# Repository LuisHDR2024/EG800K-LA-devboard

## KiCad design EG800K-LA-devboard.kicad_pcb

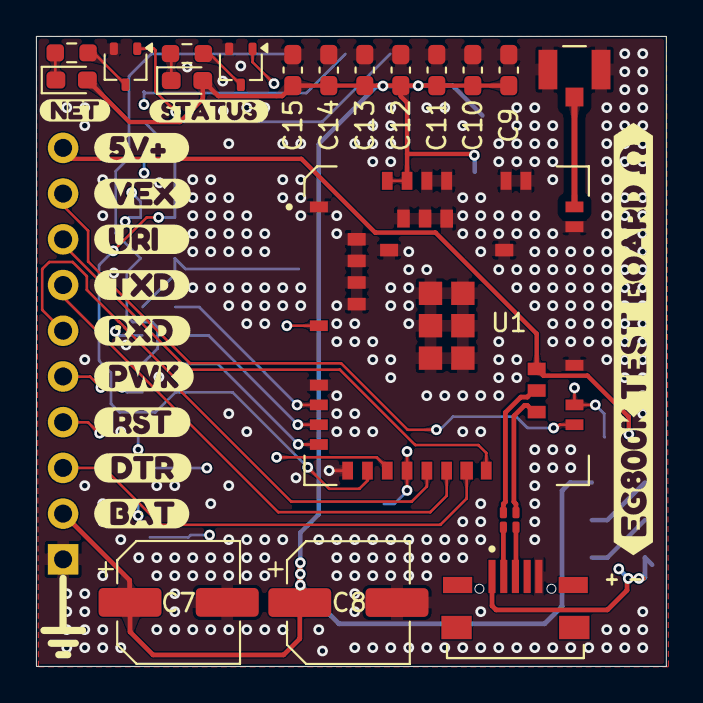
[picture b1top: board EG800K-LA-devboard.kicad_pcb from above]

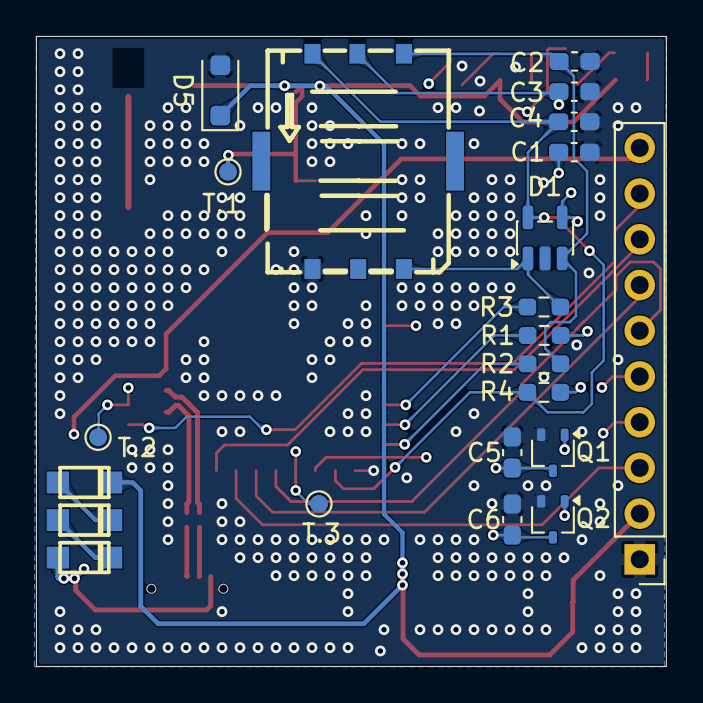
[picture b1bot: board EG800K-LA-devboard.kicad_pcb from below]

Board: 4 copper layers, 35.0 x 35.0 mm, 51 parts (19 on the bottom side), 32 nets.

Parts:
C1, C2, C3: 33pF; C_0603_1608Metric_Pad1.08x0.95mm_HandSolder
C4, C11: 100nf; C_0603_1608Metric_Pad1.08x0.95mm_HandSolder
C5, C6, C12: 10nf; C_0603_1608Metric_Pad1.08x0.95mm_HandSolder
C7, C8: 470uF; CP_Elec_6.3x7.7
C9: 47uf; C_0603_1608Metric_Pad1.08x0.95mm_HandSolder
C10: 33pf; C_0603_1608Metric_Pad1.08x0.95mm_HandSolder
C13: 0.1uf; C_0603_1608Metric_Pad1.08x0.95mm_HandSolder
C14: 1uf; C_0603_1608Metric_Pad1.08x0.95mm_HandSolder
C15: 10uf; C_0603_1608Metric_Pad1.08x0.95mm_HandSolder
D1: ESDA6V1SC5; SOT-23-5
D2, D3, D4: KUU SS36; KUU_SS36_foot
D5: SMFJ5.0A; D_SOD-123F
D6, D7: LED; LED_0603_1608Metric_Pad1.05x0.95mm_HandSolder
J1: U.FL-R-SMT_10_; U.FL-R-SMT_10_-foot
J2: MICROQTJ; MICROQTJ-foot
J4: Conn_01x11_Pin; PinHeader_1x10_P2.54mm_Vertical
NANO-SIM-0501A-P1: NANO-SIM-0501A-P; nano-sim-0501a-p_foot
Q1, Q2, Q4, Q5: DTC143ZUAT106; SOT-323_SC-70
R1, R2, R3: 0; R_0603_1608Metric_Pad0.98x0.95mm_HandSolder
R4: 15k; R_0603_1608Metric_Pad0.98x0.95mm_HandSolder
R5, R6: 22; R_0201_0603Metric_Pad0.64x0.40mm_HandSolder
R7, R8: 2.2k; R_0603_1608Metric_Pad0.98x0.95mm_HandSolder
U1: EG800KEULC-I03-SNNSA; Quectel_EG800K_foot_recorted
kibuzzard-6A1B8E1D: G***; kibuzzard-6A1B8E1D
kibuzzard-6A166AE0: G***; kibuzzard-6A166AE0
kibuzzard-6A166AEF: G***; kibuzzard-6A166AEF
kibuzzard-6A7814A6: G***; kibuzzard-6A7814A6
kibuzzard-6A7814D1: G***; kibuzzard-6A7814D1
kibuzzard-6A7814E0: G***; kibuzzard-6A7814E0
kibuzzard-6A7814F3: G***; kibuzzard-6A7814F3
kibuzzard-6A78147A: G***; kibuzzard-6A78147A
kibuzzard-6A78152D: G***; kibuzzard-6A78152D
kibuzzard-6A781493: G***; kibuzzard-6A781493
kibuzzard-6A781522: G***; kibuzzard-6A781522
kibuzzard-6A781536: G***; kibuzzard-6A781536

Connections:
+5V: D2.A, J2.1 (VCC), J4.10, U1.61 (USB_VBUS)
/DC 3.8v supply: C7.1, C8.1, C9.2, C10.2, C11.2, C12.2, C13.2, C14.2, C15.2, D4.C, D5.1 (K), D6.2 (A), D7.2 (A), J4.2, U1.42 (VBAT), U1.43 (VBAT__1)
/EG800K.NET_STATUS: Q5.1 (B), U1.16 (NET_STATUS)
/EG800K.PWRKEY: C5.2, Q1.3 (C), U1.7 (PWRKEY)
/EG800K.RESET: C6.2, Q2.3 (C), U1.15 (~RESET)
/EG800K.STATUS: Q4.1 (B), U1.25 (STATUS)
/EG800K.UART1_RXD: J4.6, U1.17 (MAIN_RXD)
/EG800K.UART1_Ri: J4.8, U1.20 (MAIN_RI)
/EG800K.UART1_TXD: J4.7, U1.18 (MAIN_TXD)
/EG800K.USB_D+: R6.2, U1.59 (USB_DP)
/EG800K.USB_D-: R5.2, U1.60 (USB_DM)
/EG800K.VDD_ETX: J4.9, U1.24 (VDD_EXT)
/HOST.EG800K.PWRKEY: J4.5, Q1.1 (B)
/HOST.EG800K.RESET: J4.4, Q2.1 (B)
/RF_ANT: J1.SIG, U1.35 (ANT_MAIN)
/SIM_CLK: R2.1, U1.13 (USIM_CLK)
/SIM_DATA: R3.1, U1.11 (USIM_DATA)
/SIM_RST: R1.1, U1.12 (USIM_RST)
/SIM_VDD: C4.2, D1.5 (K), NANO-SIM-0501A-P1.C1 (VCC), R4.2, U1.14 (USIM_VDD)
GND: C1.1, C2.1, C3.1, C4.1, C5.1, C6.1, C7.2, C8.2, C9.1, C10.1, C11.1, C12.1, C13.1, C14.1, C15.1, D1.2 (A), D5.2 (A), J1.G1, J1.G2, J2.5 (GND), J4.1, NANO-SIM-0501A-P1.C5 (GND), Q1.2 (E), Q2.2 (E), Q4.2 (E), Q5.2 (E), U1.1 (GND_1), U1.10 (GND_1__1), U1.27 (GND_1__2), U1.34 (GND_1__3), U1.36 (GND_1__4), U1.37 (GND_1__5), U1.40 (GND_1__6), U1.41 (GND_1__7), U1.45 (GND_1__8), U1.46 (GND_1__9), U1.47 (GND_1__10), U1.48 (GND_1__11), U1.70 (GND_2), U1.71 (GND_2__1), U1.72 (GND_2__2), U1.73 (GND_2__3), U1.88 (GND_2__4), U1.89 (GND_2__5), U1.90 (GND_2__6), U1.91 (GND_2__7), U1.92 (GND_2__8), U1.93 (GND_2__9), U1.94 (GND_2__10), U1.95 (GND_2__11)
unnamed: C1.2, R4.1
unnamed: D2.C, D3.A
unnamed: D3.C, D4.A
unnamed: D6.1 (K), R7.2
unnamed: D7.1 (K), R8.2
unnamed: J2.3 (D+), R6.1
unnamed: J2.2 (D-), R5.1
unnamed: C2.2, D1.3 (K), NANO-SIM-0501A-P1.C3 (CLK), R2.2
unnamed: D1.1 (K), NANO-SIM-0501A-P1.C7 (I/O), R3.2
unnamed: C3.2, D1.4 (K), NANO-SIM-0501A-P1.C2 (RST), R1.2
unnamed: Q4.3 (C), R7.1
unnamed: Q5.3 (C), R8.1

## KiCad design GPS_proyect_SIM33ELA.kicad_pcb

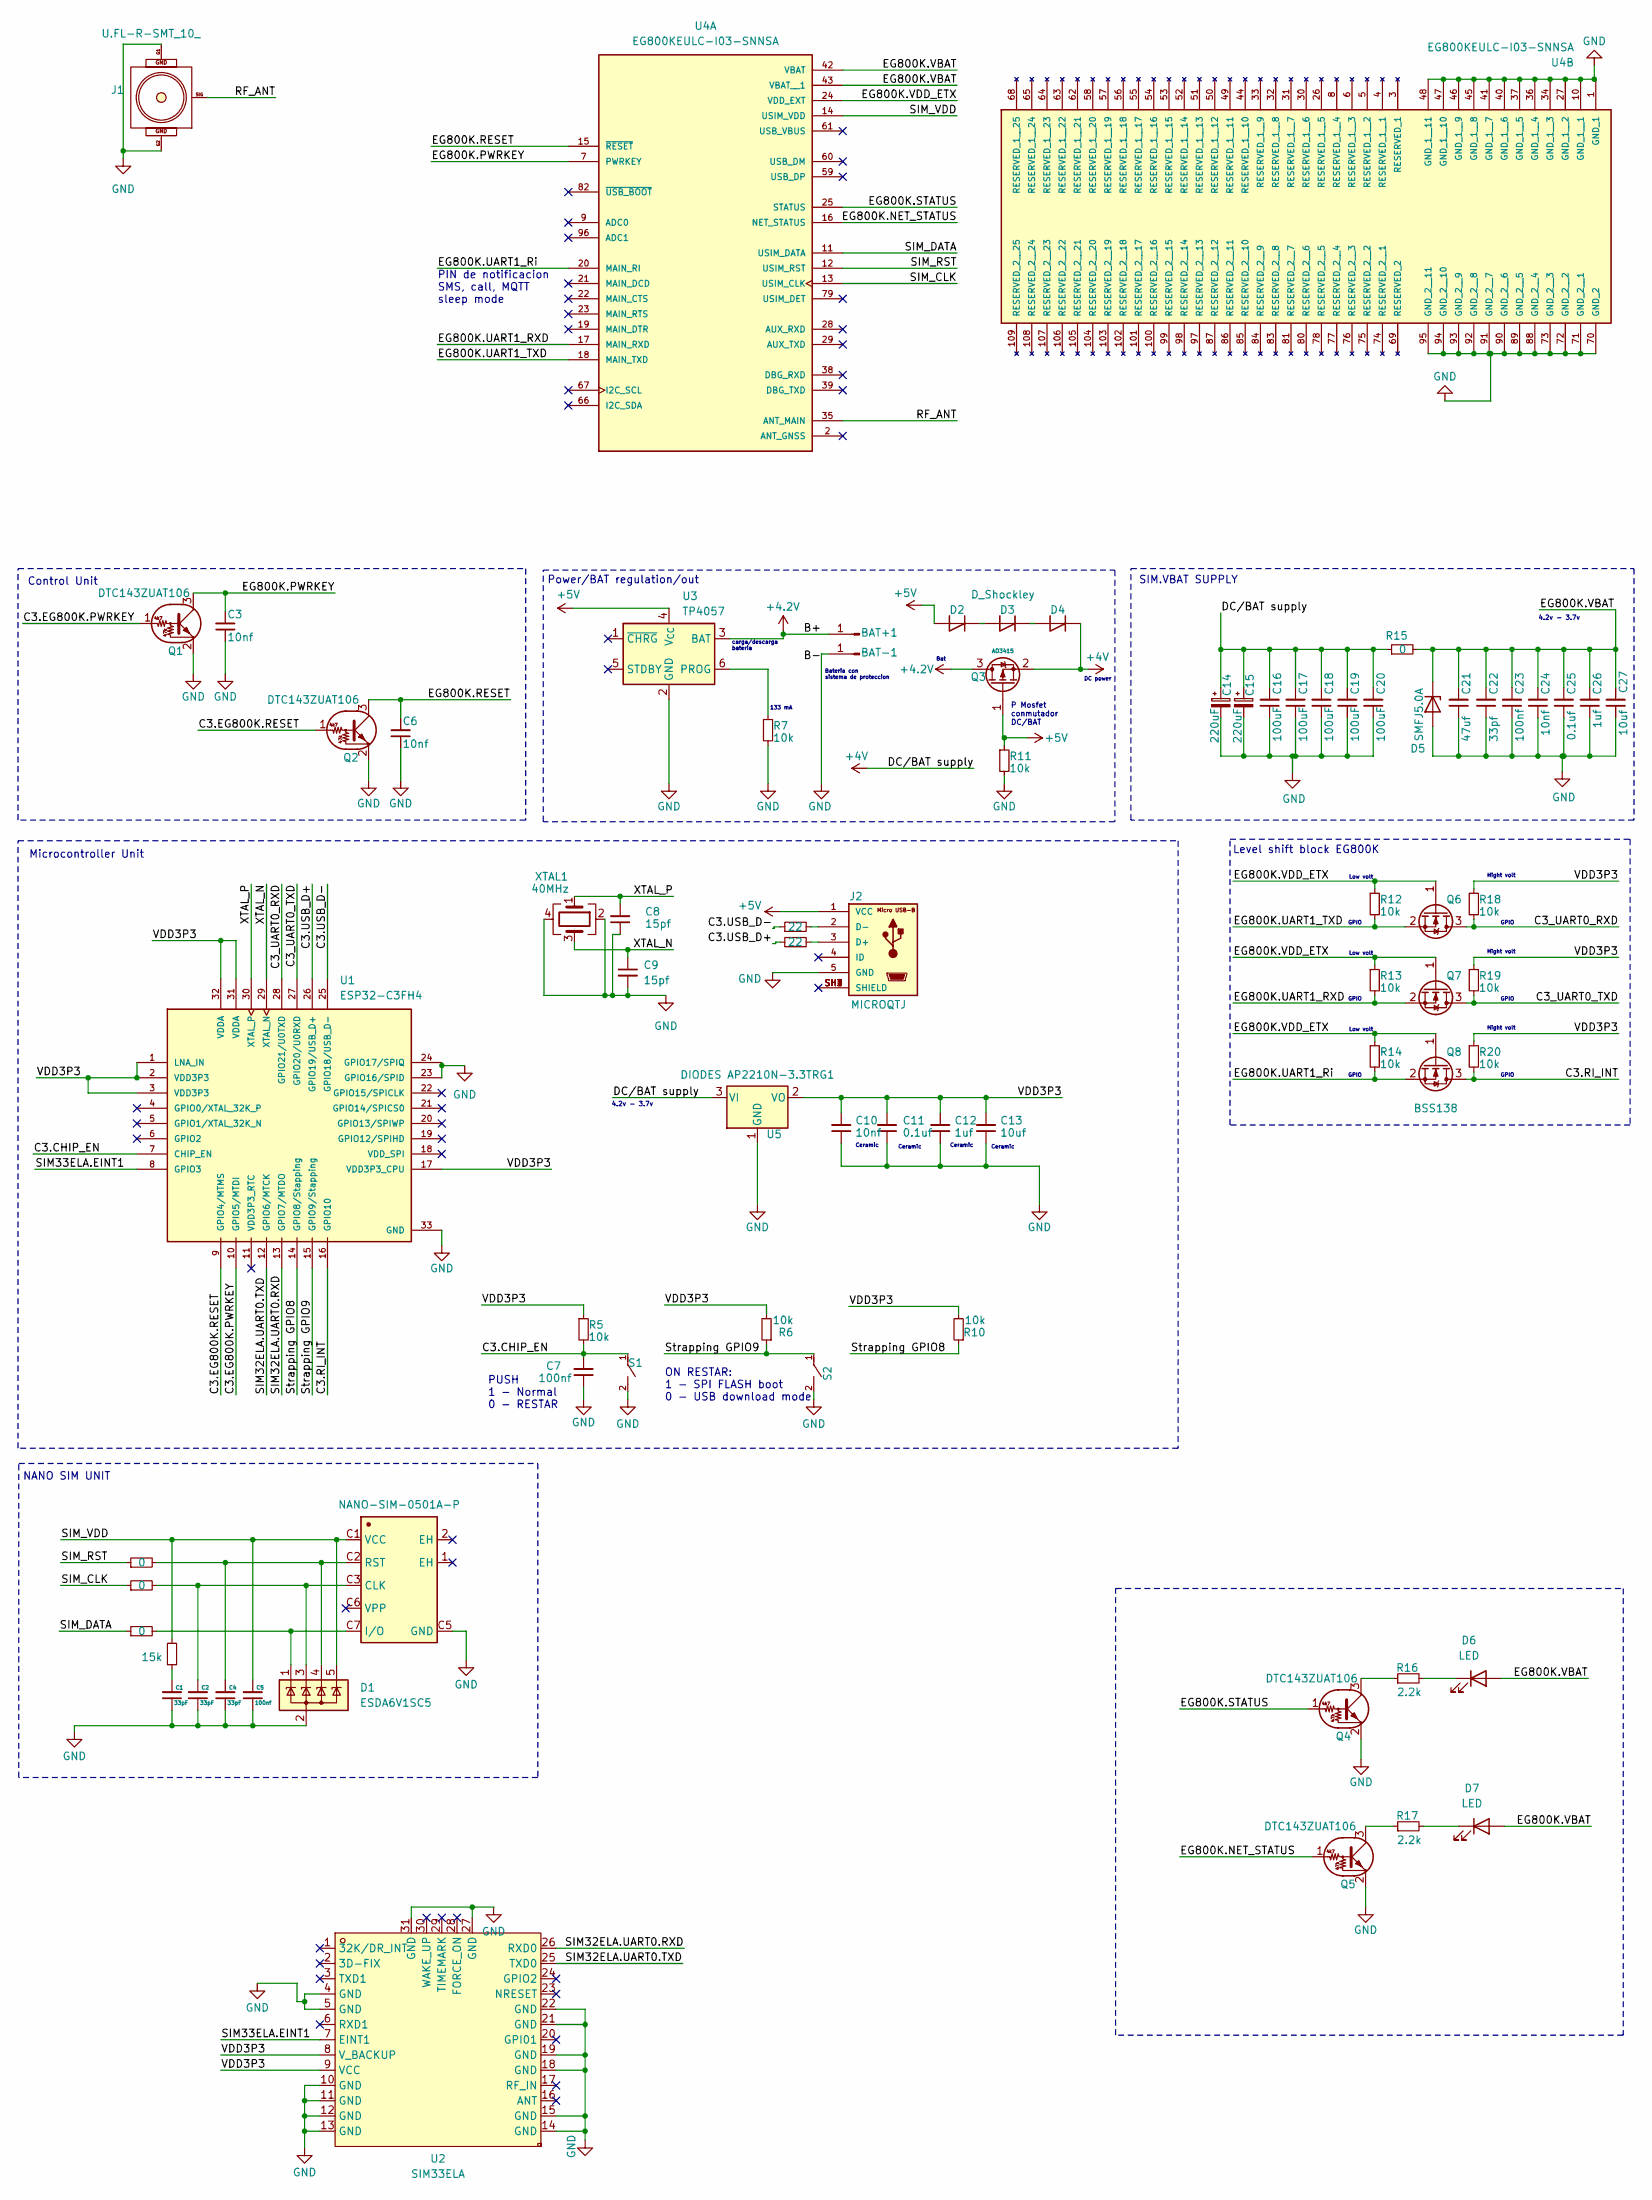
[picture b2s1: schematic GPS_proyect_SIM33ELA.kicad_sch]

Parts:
BAT+1: BAT+; SolderWirePad_1x01_SMD_2x4mm
BAT-1: BAT-; SolderWirePad_1x01_SMD_2x4mm
C1, C2, C4: 33pF; C_0603_1608Metric_Pad1.08x0.95mm_HandSolder; part number GRM1885C1H330JA01D
C3, C6, C10, C24: 10nf; C_0603_1608Metric_Pad1.08x0.95mm_HandSolder; part number GRM188R71H103KA01D
C5, C7, C23: 100nf; C_0603_1608Metric_Pad1.08x0.95mm_HandSolder; part number GRM188R71C104KA01D
C8, C9: 15pf; C_0603_1608Metric_Pad1.08x0.95mm_HandSolder; part number GRM1885C1H150JA01D
C11, C25: 0.1uf; C_0603_1608Metric_Pad1.08x0.95mm_HandSolder; part number GRM188R71C104KA01D
C12, C26: 1uf; C_0603_1608Metric_Pad1.08x0.95mm_HandSolder; part number GCM188R71E105KA64D
C13, C27: 10uf; C_0603_1608Metric_Pad1.08x0.95mm_HandSolder; part number GRM188R60J106KE47D
C14, C15: 220uF; CP_Elec_6.3x4.5; part number RVT0J221M0604
C16, C17, C18, C19, C20: 100uF; C_1210_3225Metric; part number GRM31CR60J107ME39L
C21: 47uf; C_0603_1608Metric_Pad1.08x0.95mm_HandSolder; part number GRM188R60J476ME15D
C22: 33pf; C_0603_1608Metric_Pad1.08x0.95mm_HandSolder; part number GRM1885C1H330JA01D
D1: ESDA6V1SC5; SOT-23-5; part number ESDA6V1SC5
D2, D3, D4: D_Shockley; D_SOD-123F; part number SS36
D5: SMFJ5.0A; D_SOD-123F; part number SMFJ5.0A
D6, D7: LED; LED_0603_1608Metric_Pad1.05x0.95mm_HandSolder; part number YLED0603R
J1: U.FL-R-SMT_10_; U.FL-R-SMT_10_-foot; part number U.FL-R-SMT-1(80)
J2: MICROQTJ; MICROQTJ-foot; part number MicroQTJ
NANO-SIM-0501A-P1: NANO-SIM-0501A-P; nano-sim-0501a-p_foot; part number NANO-SIM-0501A-P
Q1, Q2, Q4, Q5: DTC143ZUAT106; SOT-323_SC-70; part number DTC143ZUAT106
Q3: AO3415; SOT-23; part number AO3415
Q6, Q7, Q8: BSS138; SOT-23; part number BSS138-7-F
R1, R2, R3, R15: 0; R_0603_1608Metric_Pad0.98x0.95mm_HandSolder; part number CRCW06030000Z0EA
R4: 15k; R_0603_1608Metric_Pad0.98x0.95mm_HandSolder; part number CRCW06030000Z0EA
R5, R6, R7, R10, R11, R12, R13, R14, R18, R19, R20: 10k; R_0603_1608Metric_Pad0.98x0.95mm_HandSolder; part number CRCW060310K0FKEA
R8, R9: 22; R_0603_1608Metric_Pad0.98x0.95mm_HandSolder; part number CRCW060322R0FKEA
R16, R17: 2.2k; R_0603_1608Metric_Pad0.98x0.95mm_HandSolder; part number CRCW06032K20FKEAC
S1, S2: TS-1088-AR02016; SW_TS-1088-AR02016; part number TS-1088-AR02016
U1: ESP32-C3FH4; ESP32-C3FH4_foot; part number ESP32-C3FH4
U2: SIM33ELA; SIM33ELA_v2; part number SIM33ELA; LCSC Part C6488289
U3: TP4057; TSOT-23-6; part number TP4057
U4: EG800KEULC-I03-SNNSA; Quectel_EG800K_foot; part number Quectel EG800K-LA
U5: DIODES AP2210N-3.3TRG1; SOT-23; part number AP2210N-3.3TRG1
XTAL1: 40MHz; Crystal_SMD_3225-4Pin_3.2x2.5mm; part number XL2EL89CPI-111YLC-40M

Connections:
+4.2V: BAT+1.1, Q3.3 (D), U3.3 (BAT)
+4V: C14.1, C15.1, C16.2, C17.2, C18.2, C19.2, C20.2, D4.1 (K), Q3.2 (S), R15.1, U5.3 (VI)
+5V: D2.2 (A), J2.1 (VCC), Q3.1 (G), R11.1, U3.4 (V_{CC})
/C3.CHIP_EN: C7.2, R5.2, S1.1, U1.7 (CHIP_EN)
/C3.EG800K.PWRKEY: Q1.1 (B), U1.10 (GPIO5/MTDI)
/C3.EG800K.RESET: Q2.1 (B), U1.9 (GPIO4/MTMS)
/C3.RI_INT: Q8.3 (D), R20.2, U1.16 (GPIO10)
/C3.USB_D+: R9.1, U1.26 (GPIO19/USB_D+)
/C3.USB_D-: R8.1, U1.25 (GPIO18/USB_D-)
/C3_UART0_RXD: Q6.3 (D), R18.2, U1.28 (GPIO21/U0TXD)
/C3_UART0_TXD: Q7.3 (D), R19.2, U1.27 (GPIO20/U0RXD)
/EG800K.NET_STATUS: Q5.1 (B), U4.16 (NET_STATUS)
/EG800K.PWRKEY: C3.2, Q1.3 (C), U4.7 (PWRKEY)
/EG800K.RESET: C6.2, Q2.3 (C), U4.15 (~RESET)
/EG800K.STATUS: Q4.1 (B), U4.25 (STATUS)
/EG800K.UART1_RXD: Q7.2 (S), R13.2, U4.17 (MAIN_RXD)
/EG800K.UART1_Ri: Q8.2 (S), R14.2, U4.20 (MAIN_RI)
/EG800K.UART1_TXD: Q6.2 (S), R12.2, U4.18 (MAIN_TXD)
/EG800K.VBAT: C21.2, C22.2, C23.2, C24.2, C25.2, C26.2, C27.2, D5.1 (K), D6.2 (A), D7.2 (A), R15.2, U4.42 (VBAT), U4.43 (VBAT__1)
/EG800K.VDD_ETX: Q6.1 (G), Q7.1 (G), Q8.1 (G), R12.1, R13.1, R14.1, U4.24 (VDD_EXT)
/RF_ANT: J1.SIG, U4.35 (ANT_MAIN)
/SIM32ELA.UART0.RXD: U1.13 (GPIO7/MTDO), U2.26 (RXD0)
/SIM32ELA.UART0.TXD: U1.12 (GPIO6/MTCK), U2.25 (TXD0)
/SIM33ELA.EINT1: U1.8 (GPIO3), U2.7 (EINT1)
/SIM_CLK: R2.1, U4.13 (USIM_CLK)
/SIM_DATA: R3.1, U4.11 (USIM_DATA)
/SIM_RST: R1.1, U4.12 (USIM_RST)
/SIM_VDD: C5.2, D1.5 (K), NANO-SIM-0501A-P1.C1 (VCC), R4.2, U4.14 (USIM_VDD)
/Strapping GPIO8: R10.1, U1.14 (GPIO8/Stapping)
/Strapping GPIO9: R6.1, S2.1, U1.15 (GPIO9/Stapping)
/VDD3P3: C10.2, C11.2, C12.2, C13.2, R5.1, R6.2, R10.2, R18.1, R19.1, R20.1, U1.1 (LNA_IN), U1.2 (VDD3P3), U1.3 (VDD3P3), U1.17 (VDD3P3_CPU), U1.31 (VDDA), U1.32 (VDDA), U2.8 (V_BACKUP), U2.9 (VCC), U5.2 (VO)
/XTAL_N: C9.1, U1.29 (XTAL_N), XTAL1.3
/XTAL_P: C8.2, U1.30 (XTAL_P), XTAL1.1
GND: BAT-1.1, C1.1, C2.1, C3.1, C4.1, C5.1, C6.1, C7.1, C8.1, C9.2, C10.1, C11.1, C12.1, C13.1, C14.2, C15.2, C16.1, C17.1, C18.1, C19.1, C20.1, C21.1, C22.1, C23.1, C24.1, C25.1, C26.1, C27.1, D1.2 (A), D5.2 (A), J1.G1, J1.G2, J2.5 (GND), NANO-SIM-0501A-P1.C5 (GND), Q1.2 (E), Q2.2 (E), Q4.2 (E), Q5.2 (E), R7.2, R11.2, S1.2, S2.2, U1.23 (GPIO16/SPID), U1.24 (GPIO17/SPIQ), U1.33 (GND), U2.4 (GND), U2.5 (GND), U2.10 (GND), U2.11 (GND), U2.12 (GND), U2.13 (GND), U2.14 (GND), U2.15 (GND), U2.18 (GND), U2.19 (GND), U2.21 (GND), U2.22 (GND), U2.27 (GND), U2.31 (GND), U3.2 (GND), U4.1 (GND_1), U4.10 (GND_1__1), U4.27 (GND_1__2), U4.34 (GND_1__3), U4.36 (GND_1__4), U4.37 (GND_1__5), U4.40 (GND_1__6), U4.41 (GND_1__7), U4.45 (GND_1__8), U4.46 (GND_1__9), U4.47 (GND_1__10), U4.48 (GND_1__11), U4.70 (GND_2), U4.71 (GND_2__1), U4.72 (GND_2__2), U4.73 (GND_2__3), U4.88 (GND_2__4), U4.89 (GND_2__5), U4.90 (GND_2__6), U4.91 (GND_2__7), U4.92 (GND_2__8), U4.93 (GND_2__9), U4.94 (GND_2__10), U4.95 (GND_2__11), U5.1 (GND), XTAL1.2, XTAL1.4
unnamed: C1.2, R4.1
unnamed: D2.1 (K), D3.2 (A)
unnamed: D3.1 (K), D4.2 (A)
unnamed: D6.1 (K), R16.2
unnamed: D7.1 (K), R17.2
unnamed: J2.3 (D+), R9.2
unnamed: J2.2 (D-), R8.2
unnamed: C2.2, D1.3 (K), NANO-SIM-0501A-P1.C3 (CLK), R2.2
unnamed: D1.1 (K), NANO-SIM-0501A-P1.C7 (I/O), R3.2
unnamed: C4.2, D1.4 (K), NANO-SIM-0501A-P1.C2 (RST), R1.2
unnamed: Q4.3 (C), R16.1
unnamed: Q5.3 (C), R17.1
unnamed: R7.1, U3.6 (PROG)

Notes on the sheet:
SIM.VBAT SUPPLY
Ceramic
Bateria con sistema de proteccion
ON RESTAR: 1 - SPI FLASH boot 0 - USB download mode
carga/descarga bateria
Hight volt
GPIO
PUSH 1 - Normal 0 - RESTAR
Low volt
4.2v - 3.7v
Bat
P Mosfet conmutador DC/BAT
Control Unit
DC power
PIN de notificacion SMS, call, MQTT sleep mode
133 mA
Microcontroller Unit
Level shift block EG800K
Power/BAT regulation/out
NANO SIM UNIT

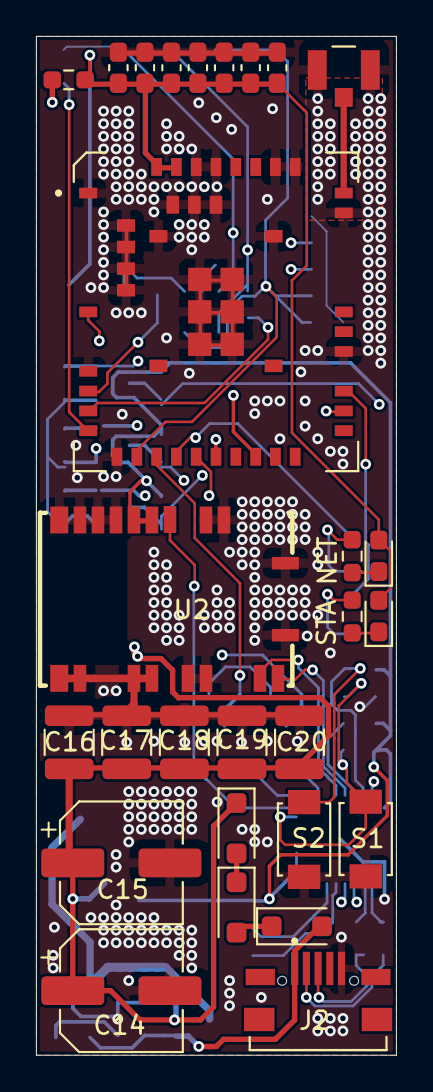
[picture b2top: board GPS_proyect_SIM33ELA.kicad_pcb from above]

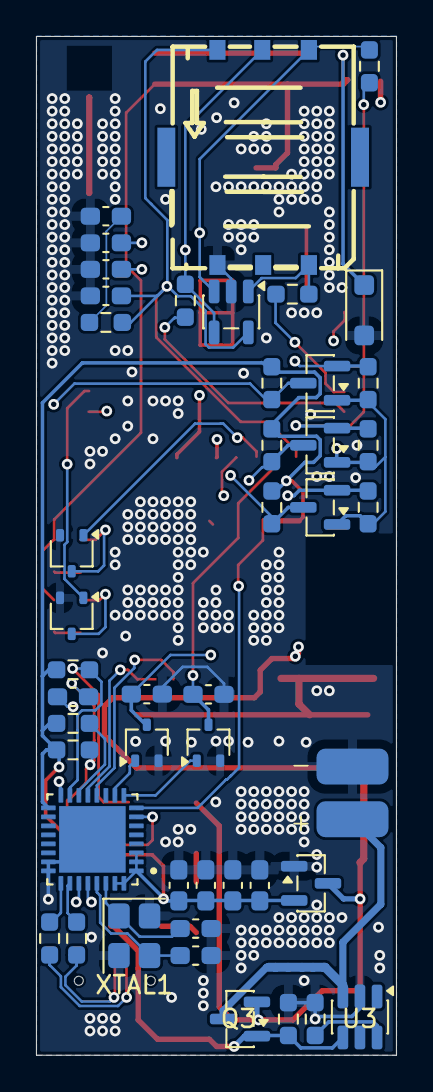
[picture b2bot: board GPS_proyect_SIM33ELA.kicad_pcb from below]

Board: 4 copper layers, 20.0 x 56.6 mm, 75 parts (47 on the bottom side), 46 nets.

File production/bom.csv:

Designator,Footprint,Quantity,Value,LCSC Part #
"C1, C2, C22, C4",0603,4,33pF,
C21,0603,1,47uf,
"C23, C5",0603,2,100nf,
"C24, C3, C6",0603,3,10nf,
C25,0603,1,0.1uf,
C26,0603,1,1uf,
C27,0603,1,10uf,
"C7, C8",CP_Elec_6.3x7.7,2,470uF,
D1,SOT-23-5,1,ESDA6V1SC5,
"D3, D4, D8",KUU_SS36_foot,3,KUU SS36,
D5,D_SOD-123F,1,SMFJ5.0A,
"D6, D7",0603,2,LED,
FL2,FILTER-SMD_4P-L2.0-W1.2-BL_DLW21H,1,Choke_CommonMode_FerriteCore_1243,
J1,U.FL-R-SMT_10_-foot,1,U.FL-R-SMT_10_,
J2,MICROQTJ-foot,1,MICROQTJ,
J5,PinHeader_1x08_P2.54mm_Vertical,1,Conn_01x08_Pin,
NANO-SIM-0501A-P1,nano-sim-0501a-p_foot,1,NANO-SIM-0501A-P,
"Q1, Q2, Q4, Q5",SOT-323_SC-70,4,DTC143ZUAT106,
"Q6, Q7, Q8",SOT-23,3,BSS138,
"R1, R15, R2, R3",0603,4,0,
"R12, R13, R14, R18, R19, R20",0603,6,10k,
"R16, R17",0603,2,2.2k,
R4,0603,1,15k,
U4,Quectel_EG800K_foot_recorted,1,EG800KEULC-I03-SNNSA,

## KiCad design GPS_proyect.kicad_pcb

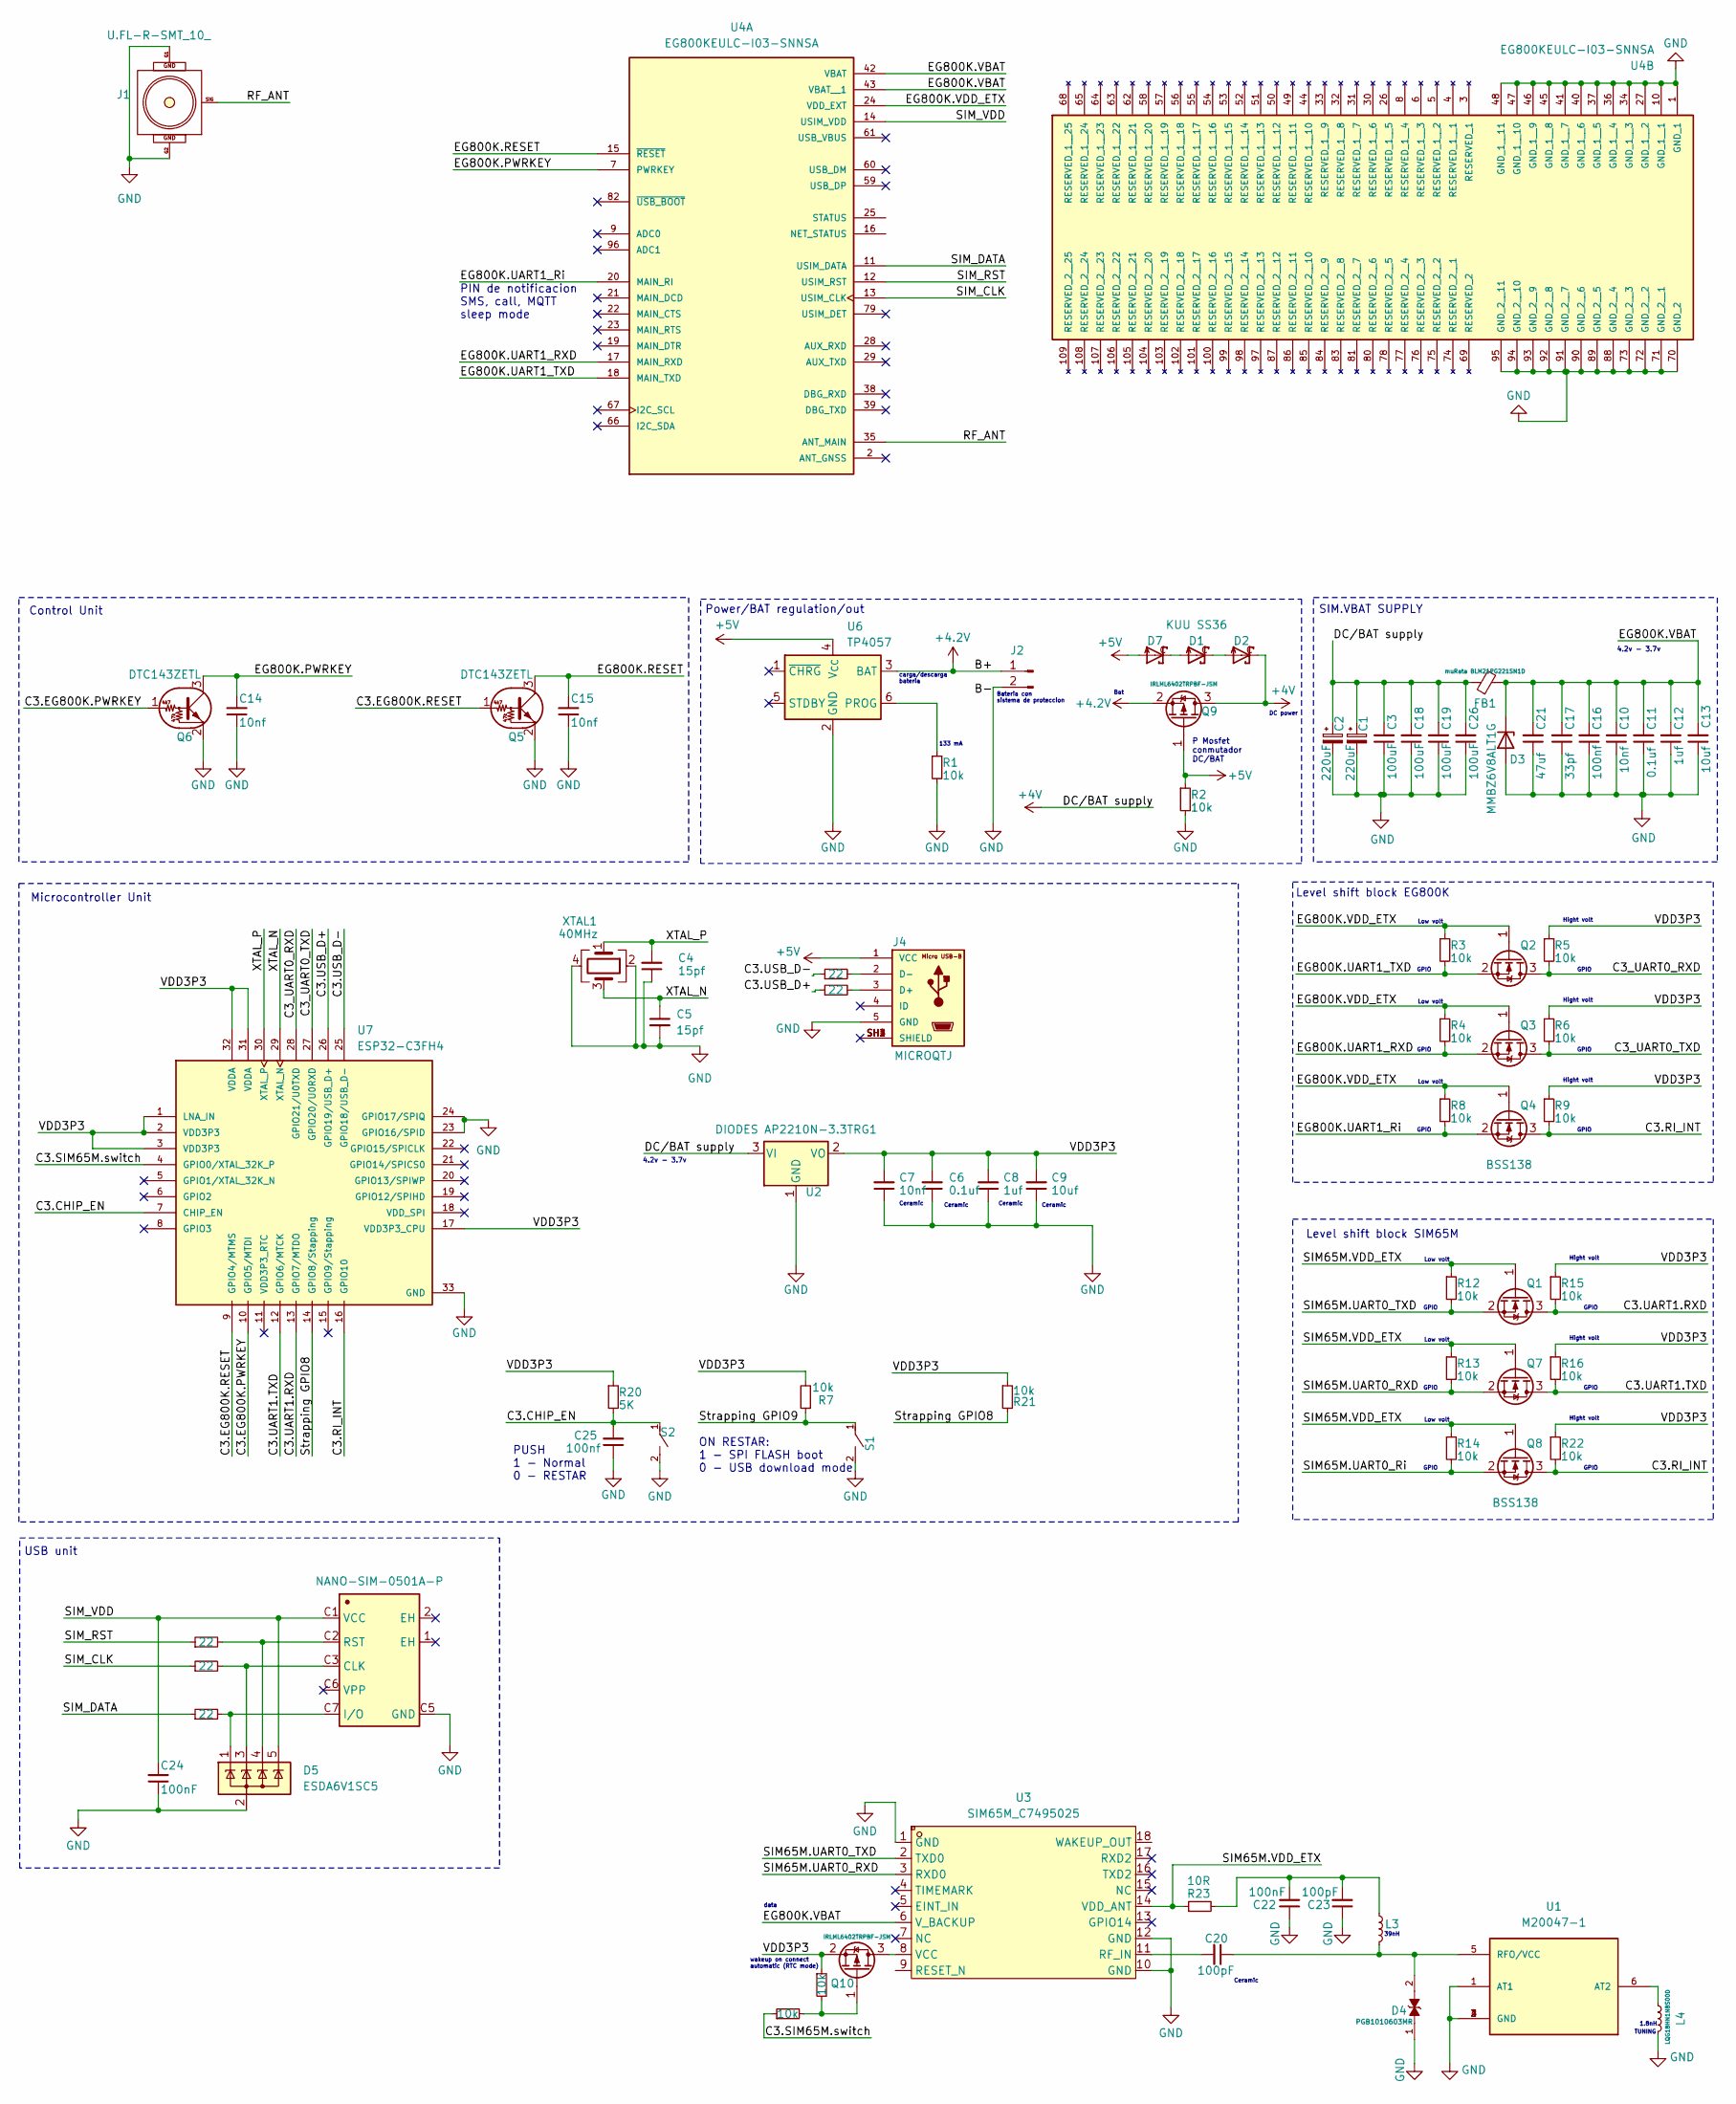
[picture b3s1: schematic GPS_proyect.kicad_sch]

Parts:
C1, C2: 220uF; CP_Elec_6.3x4.5
C3, C18, C19, C26: 100uF; C_0805_2012Metric
C4, C5: 15pf; C_0603_1608Metric_Pad1.08x0.95mm_HandSolder
C6, C11: 0.1uf; C_0603_1608Metric_Pad1.08x0.95mm_HandSolder
C7, C10, C14, C15: 10nf; C_0603_1608Metric_Pad1.08x0.95mm_HandSolder
C8, C12: 1uf; C_0603_1608Metric_Pad1.08x0.95mm_HandSolder
C9, C13: 10uf; C_0603_1608Metric_Pad1.08x0.95mm_HandSolder
C16, C25: 100nf; C_0603_1608Metric_Pad1.08x0.95mm_HandSolder
C17: 33pf; C_0603_1608Metric_Pad1.08x0.95mm_HandSolder
C20, C23: 100pF; C_0603_1608Metric_Pad1.08x0.95mm_HandSolder
C21: 47uf; C_0603_1608Metric_Pad1.08x0.95mm_HandSolder
C22, C24: 100nF; C_0603_1608Metric_Pad1.08x0.95mm_HandSolder
D1, D2, D7: KUU SS36; KUU_SS36_foot
D3: MMBZ6V8ALT1G; D_SOD-523
D4: PGB1010603MR; DIOC1608X36N; PARTREV 07/27/15
D5: ESDA6V1SC5; SOT-23-5
FB1: muRata BLM21PG221SN1D; C_0805_2012Metric_Pad1.18x1.45mm_HandSolder
J1: U.FL-R-SMT_10_; U.FL-R-SMT_10_-foot; PARTREV 11.11.15
J2: Conn_01x02_Pin; TE_440055-2_1x02_P2.00mm_Horizontal
J4: MICROQTJ; MICROQTJ-foot; PARTREV A/0
L3: LQW18AN47NG00D; L_0603_1608Metric_Pad1.05x0.95mm_HandSolder
L4: LQG18HN1N8S00D; L_0603_1608Metric_Pad1.05x0.95mm_HandSolder
NANO-SIM-0501A-P1: NANO-SIM-0501A-P; nano-sim-0501a-p_foot; LCSC Part C29780392
Q1, Q2, Q3, Q4, Q7, Q8: BSS138; SOT-23
Q5, Q6: DTC143ZETL; SOT-23
Q9, Q10: IRLML6402TRPBF-JSM; SOT-23
R1, R2, R3, R4, R5, R6, R7, R8, R9, R12, R13, R14, R15, R16, R21, R22, R24, R25: 10k; R_0603_1608Metric_Pad0.98x0.95mm_HandSolder
R10, R11, R17, R18, R19: 22; R_0603_1608Metric_Pad0.98x0.95mm_HandSolder
R20: 5K; R_0603_1608Metric_Pad0.98x0.95mm_HandSolder
R23: 10R; R_0603_1608Metric_Pad0.98x0.95mm_HandSolder
S1, S2: TS-1088-AR02016; SW_TS-1088-AR02016; PARTREV N/A
U1: M20047-1; M20047-1_foot; PARTREV April 2018
U2: DIODES AP2210N-3.3TRG1; SOT-23
U3: SIM65M_C7495025; SIM65M_foot; LCSC Part C7495025
U4: EG800KEULC-I03-SNNSA; Quectel_EG800K_foot; PARTREV 1.1
U6: TP4057; TSOT-23-6
U7: ESP32-C3FH4; ESP32-C3FH4_foot; PARTREV 2.0
XTAL1: 40MHz; Crystal_SMD_3225-4Pin_3.2x2.5mm

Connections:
+4.2V: J2.1, Q9.2 (S), U6.3 (BAT)
+4V: C1.1, C2.1, C3.2, C18.2, C19.2, C26.2, D2.C, FB1.1, Q9.3 (D), U2.3 (VI)
+5V: D7.A, J4.1 (VCC), Q9.1 (G), R2.1, U6.4 (V_{CC})
/C3.CHIP_EN: C25.2, R20.2, S2.1, U7.7 (CHIP_EN)
/C3.EG800K.PWRKEY: Q6.1 (B), U7.10 (GPIO5/MTDI)
/C3.EG800K.RESET: Q5.1 (B), U7.9 (GPIO4/MTMS)
/C3.RI_INT: Q4.3 (D), Q8.3 (D), R9.2, R22.2, U7.16 (GPIO10)
/C3.SIM65M.switch: R25.1, U7.4 (GPIO0/XTAL_32K_P)
/C3.UART1.RXD: Q1.3 (D), R15.2, U7.13 (GPIO7/MTDO)
/C3.UART1.TXD: Q7.3 (D), R16.2, U7.12 (GPIO6/MTCK)
/C3.USB_D+: R11.1, U7.26 (GPIO19/USB_D+)
/C3.USB_D-: R10.1, U7.25 (GPIO18/USB_D-)
/C3_UART0_RXD: Q2.3 (D), R5.2, U7.28 (GPIO21/U0TXD)
/C3_UART0_TXD: Q3.3 (D), R6.2, U7.27 (GPIO20/U0RXD)
/EG800K.PWRKEY: C14.2, Q6.3 (C), U4.7 (PWRKEY)
/EG800K.RESET: C15.2, Q5.3 (C), U4.15 (~RESET)
/EG800K.UART1_RXD: Q3.2 (S), R4.2, U4.17 (MAIN_RXD)
/EG800K.UART1_Ri: Q4.2 (S), R8.2, U4.20 (MAIN_RI)
/EG800K.UART1_TXD: Q2.2 (S), R3.2, U4.18 (MAIN_TXD)
/EG800K.VBAT: C10.2, C11.2, C12.2, C13.2, C16.2, C17.2, C21.2, D3.1 (K), FB1.2, U3.6 (V_BACKUP), U4.42 (VBAT), U4.43 (VBAT__1)
/EG800K.VDD_ETX: Q2.1 (G), Q3.1 (G), Q4.1 (G), R3.1, R4.1, R8.1, U4.24 (VDD_EXT)
/RF_ANT: J1.SIG, U4.35 (ANT_MAIN)
/SIM65M.UART0_RXD: Q7.2 (S), R13.2, U3.3 (RXD0)
/SIM65M.UART0_Ri: Q8.2 (S), R14.2
/SIM65M.UART0_TXD: Q1.2 (S), R12.2, U3.2 (TXD0)
/SIM65M.VDD_ETX: Q1.1 (G), Q7.1 (G), Q8.1 (G), R12.1, R13.1, R14.1, R23.1, U3.14 (VDD_ANT)
/SIM_CLK: R18.1, U4.13 (USIM_CLK)
/SIM_DATA: R19.1, U4.11 (USIM_DATA)
/SIM_RST: R17.1, U4.12 (USIM_RST)
/SIM_VDD: C24.2, D5.5 (K), NANO-SIM-0501A-P1.C1 (VCC), U4.14 (USIM_VDD); also elsewhere on the board
/Strapping GPIO8: R21.2, U7.14 (GPIO8/Stapping)
/Strapping GPIO9: R7.1, S1.1
/VDD3P3: C6.2, C7.2, C8.2, C9.2, Q10.2 (S), R5.1, R6.1, R7.2, R9.1, R15.1, R16.1, R20.1, R21.1, R22.1, R24.1, U2.2 (VO), U7.1 (LNA_IN), U7.2 (VDD3P3), U7.3 (VDD3P3), U7.17 (VDD3P3_CPU), U7.31 (VDDA), U7.32 (VDDA)
/XTAL_N: C5.1, U7.29 (XTAL_N), XTAL1.3
/XTAL_P: C4.2, U7.30 (XTAL_P), XTAL1.1
GND: C1.2, C2.2, C3.1, C4.1, C5.2, C6.1, C7.1, C8.1, C9.1, C10.1, C11.1, C12.1, C13.1, C14.1, C15.1, C16.1, C17.1, C18.1, C19.1, C21.1, C22.1, C23.1, C24.1, C25.1, C26.1, D3.2 (A), D4.1, D5.2 (A), J1.G1, J1.G2, J2.2, J4.5 (GND), L4.1, NANO-SIM-0501A-P1.C5 (GND), Q5.2 (E), Q6.2 (E), R1.2, R2.2, S1.2, S2.2, U1.1 (AT1), U1.2 (GND), U1.3 (GND), U1.4 (GND), U2.1 (GND), U3.1 (GND), U3.10 (GND), U3.12 (GND), U4.1 (GND_1), U4.10 (GND_1__1), U4.27 (GND_1__2), U4.34 (GND_1__3), U4.36 (GND_1__4), U4.37 (GND_1__5), U4.40 (GND_1__6), U4.41 (GND_1__7), U4.45 (GND_1__8), U4.46 (GND_1__9), U4.47 (GND_1__10), U4.48 (GND_1__11), U4.70 (GND_2), U4.71 (GND_2__1), U4.72 (GND_2__2), U4.73 (GND_2__3), U4.88 (GND_2__4), U4.89 (GND_2__5), U4.90 (GND_2__6), U4.91 (GND_2__7), U4.92 (GND_2__8), U4.93 (GND_2__9), U4.94 (GND_2__10), U4.95 (GND_2__11), U6.2 (GND), U7.23 (GPIO16/SPID), U7.24 (GPIO17/SPIQ), U7.33 (GND), XTAL1.2, XTAL1.4; also elsewhere on the board
unnamed: C22.2, C23.2, L3.2, R23.2
unnamed: D1.A, D7.C
unnamed: D1.C, D2.A
unnamed: J4.3 (D+), R11.2
unnamed: J4.2 (D-), R10.2
unnamed: D5.3 (K), NANO-SIM-0501A-P1.C3 (CLK), R18.2
unnamed: D5.1 (K), NANO-SIM-0501A-P1.C7 (I/O), R19.2
unnamed: D5.4 (K), NANO-SIM-0501A-P1.C2 (RST), R17.2
unnamed: Q10.3 (D), U3.8 (VCC)
unnamed: Q10.1 (G), R24.2, R25.2
unnamed: L4.2, U1.6 (AT2)
unnamed: C20.1, D4.2, L3.1, U1.5 (RFO/VCC)
unnamed: C20.2, U3.11 (RF_IN)
unnamed: R1.1, U6.6 (PROG)

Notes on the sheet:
GPIO
wakeup on connect automatic (RTC mode)
SIM.VBAT SUPPLY
TUNING
Ceramic
Bateria con sistema de proteccion
ON RESTAR: 1 - SPI FLASH boot 0 - USB download mode
carga/descarga bateria
Hight volt
PUSH 1 - Normal 0 - RESTAR
Low volt
4.2v - 3.7v
Bat
P Mosfet conmutador DC/BAT
data
Control Unit
DC power
39nH
PIN de notificacion SMS, call, MQTT sleep mode
Level shift block SIM65M
133 mA
1.8nH
Microcontroller Unit
Level shift block EG800K
Power/BAT regulation/out
USB unit

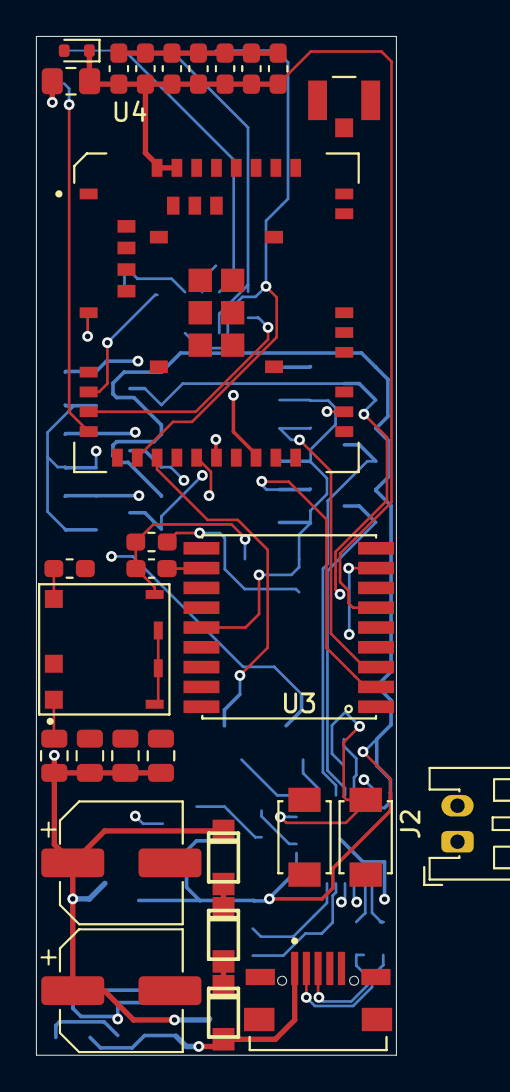
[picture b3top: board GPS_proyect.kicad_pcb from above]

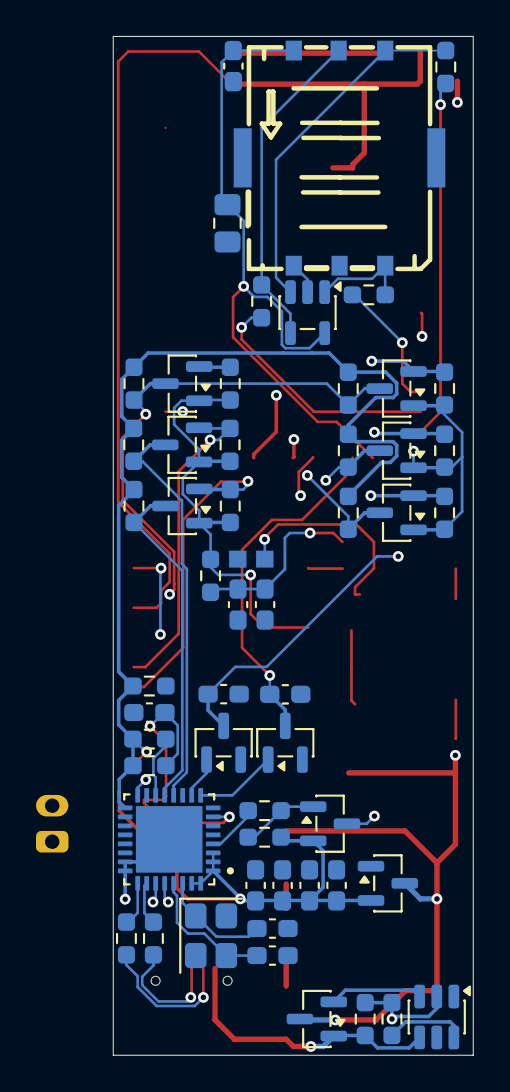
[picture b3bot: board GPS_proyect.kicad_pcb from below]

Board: 4 copper layers, 20.0 x 56.6 mm, 84 parts (55 on the bottom side), 50 nets.

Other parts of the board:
C24#2: 100nF; C_0603_1608Metric_Pad1.08x0.95mm_HandSolder

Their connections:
/SIM_VDD: C24#2.2; also elsewhere on the board
GND: C24#2.1; also elsewhere on the board

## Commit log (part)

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2026-01-24 Inicio limpio del proyecto
2026-01-27 ultima version
2026-01-28 devboard lista
2026-02-12 version final
2026-03-28 cambio stack JLC PCB, cambio USB route
2026-03-30 cambios minimos
2026-05-30 original rediseñado
2026-05-31 agregado pin de vbat y detalles
2026-06-05 carga final
2026-06-20 removido la etapa de carga de BAT
2026-06-27 Agregados res en serie en USB
